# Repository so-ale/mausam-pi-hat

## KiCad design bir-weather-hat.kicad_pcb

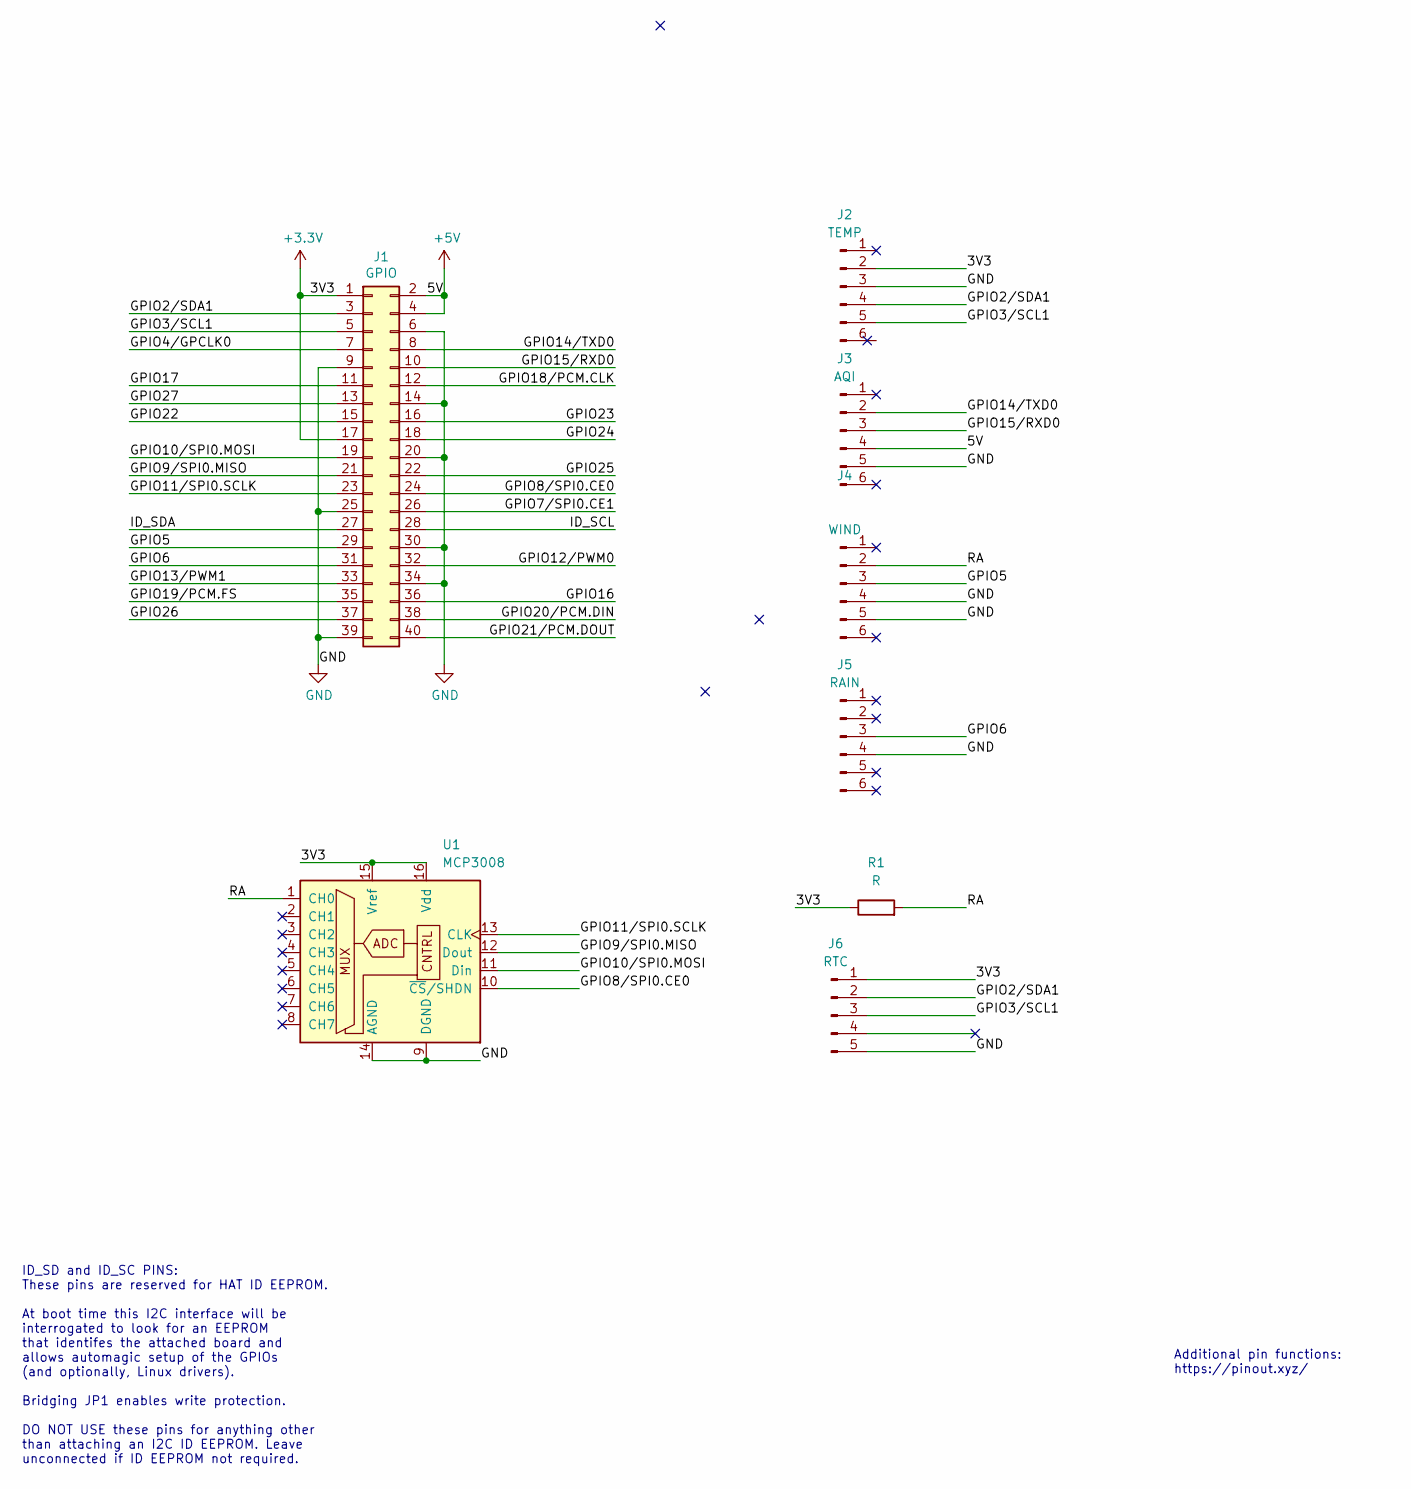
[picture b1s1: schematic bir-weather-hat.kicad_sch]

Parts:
J1: GPIO; PinSocket_2x20_P2.54mm_Vertical_SMD
J2: TEMP; RJ11-6-IND
J3: AQI; RJ11-6-IND
J4: WIND; RJ11-6-IND
J5: RAIN; RJ11-6-IND
J6: RTC; PinSocket_1x05_P2.54mm_Vertical
R1: R; R_0805_2012Metric
U1: MCP3008; SOIC-16_3.9x9.9mm_P1.27mm

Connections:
+3V3: J1.1, J1.17, J2.2, J6.1, R1.1, U1.15 (Vref), U1.16 (Vdd)
+5V: J1.2, J1.4, J3.4
/GPIO2/SDA1: J1.3, J2.4, J6.2
/GPIO3/SCL1: J1.5, J2.5, J6.3
/GPIO4/GPCLK0: J1.7
/GPIO5: J1.29, J4.3
/GPIO6: J1.31, J5.3
/GPIO7/SPI0.CE1: J1.26
/GPIO8/SPI0.CE0: J1.24, U1.10 (~CS/SHDN)
/GPIO9/SPI0.MISO: J1.21, U1.12 (Dout)
/GPIO10/SPI0.MOSI: J1.19, U1.11 (Din)
/GPIO11/SPI0.SCLK: J1.23, U1.13 (CLK)
/GPIO12/PWM0: J1.32
/GPIO13/PWM1: J1.33
/GPIO14/TXD0: J1.8, J3.2
/GPIO15/RXD0: J1.10, J3.3
/GPIO16: J1.36
/GPIO17: J1.11
/GPIO18/PCM.CLK: J1.12
/GPIO19/PCM.FS: J1.35
/GPIO20/PCM.DIN: J1.38
/GPIO21/PCM.DOUT: J1.40
/GPIO22: J1.15
/GPIO23: J1.16
/GPIO24: J1.18
/GPIO25: J1.22
/GPIO26: J1.37
/GPIO27: J1.13
/ID_SCL: J1.28
/ID_SDA: J1.27
/RA: J4.2, R1.2, U1.1 (CH0)
GND: J1.6, J1.9, J1.14, J1.20, J1.25, J1.30, J1.34, J1.39, J2.3, J3.5, J4.4, J4.5, J5.4, J6.5, U1.9 (DGND), U1.14 (AGND)

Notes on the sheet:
Additional pin functions: https://pinout.xyz/
ID_SD and ID_SC PINS: These pins are reserved for HAT ID EEPROM. At boot time this I2C interface will be interrogated to look for an EEPROM that identifes the attached board and allows automagic setup of the GPIOs (and optionally, Linux drivers). Bridging JP1 enables write protection. DO NOT USE th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

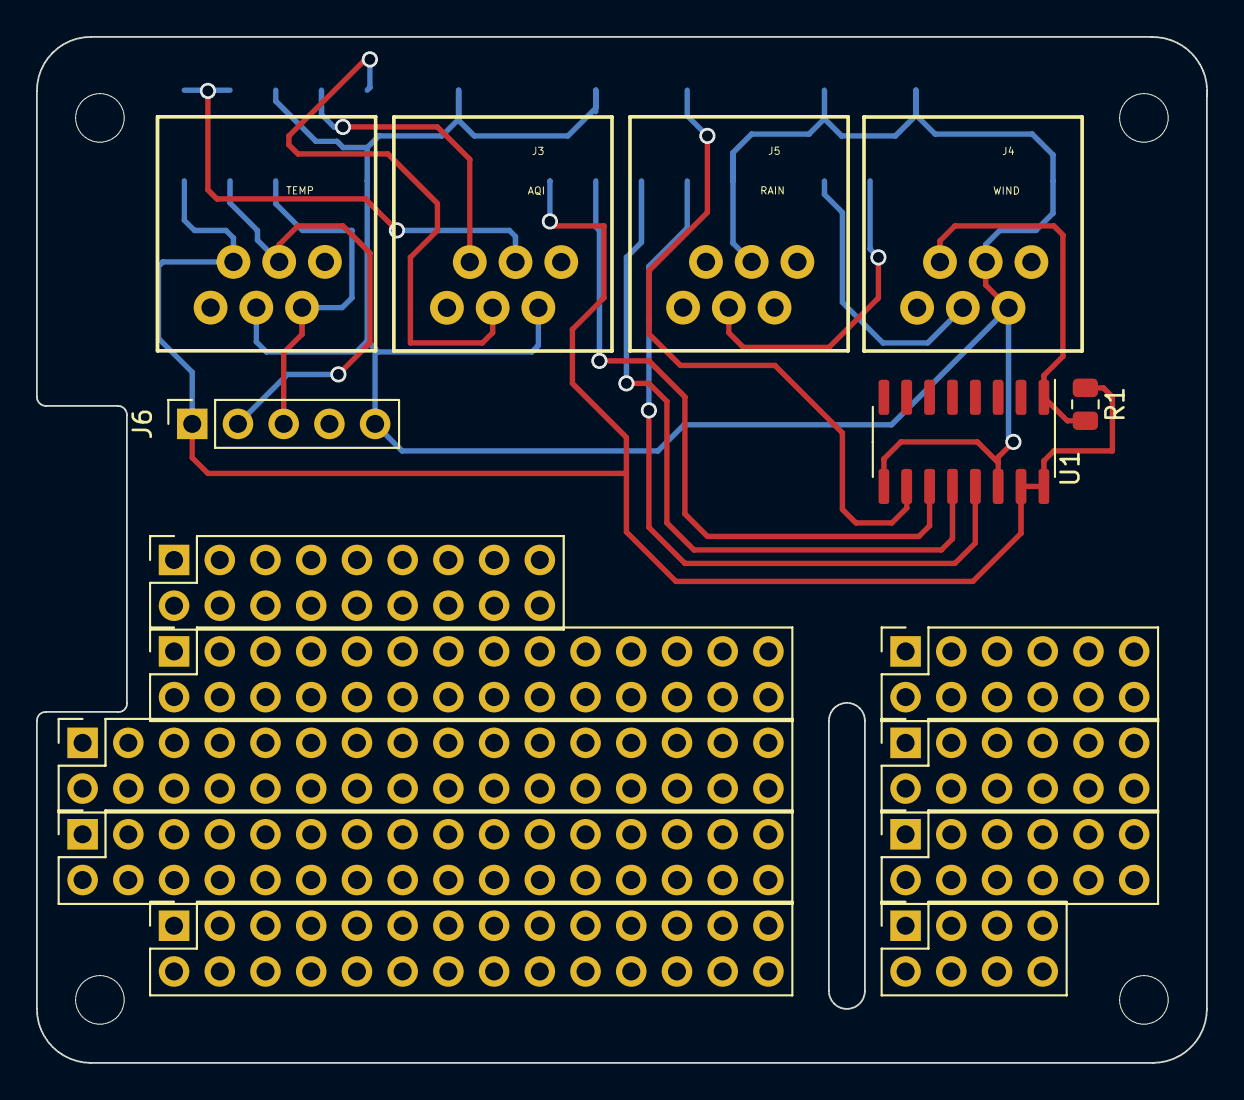
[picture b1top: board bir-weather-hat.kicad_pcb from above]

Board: 2 copper layers, 65.0 x 57.0 mm, 12 parts (1 on the bottom side), 14 nets.

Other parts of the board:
MH1, MH2, MH3, MH4: MountingHole_2.7mm_M2.5

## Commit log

2024-01-29 thhis is not the first comit
2024-01-31 Fix DFM issues
